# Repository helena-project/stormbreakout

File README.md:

stormbreakout
=============

The Helena storm breakout

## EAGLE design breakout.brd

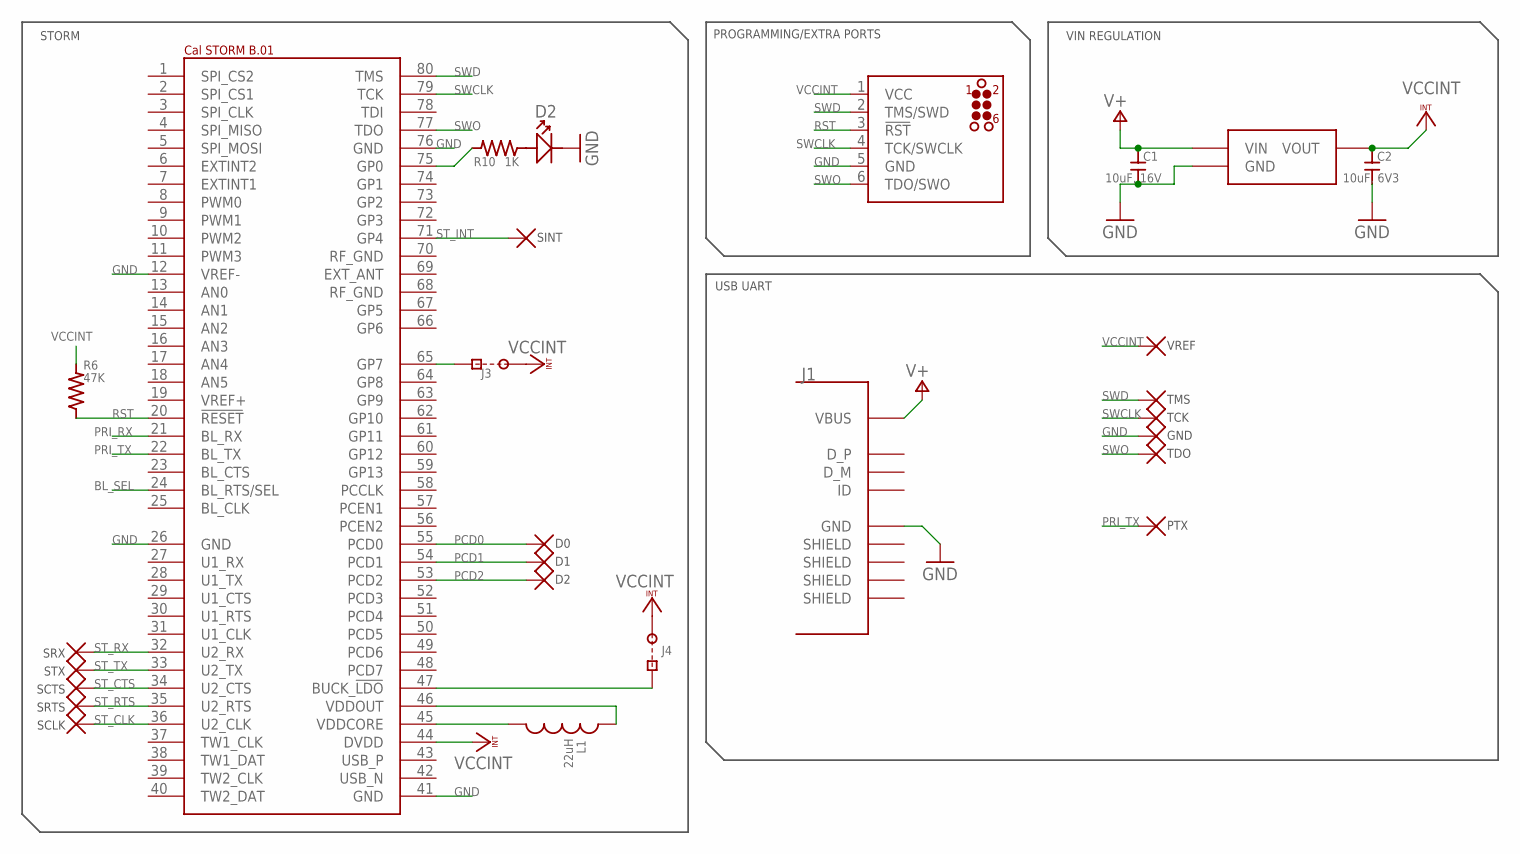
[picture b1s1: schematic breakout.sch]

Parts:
C1: 10uF, 16V; 0805
C2: 10uF, 6V3; C0603
D2: STATLED; LINE_0805
J1: USBSMT; USB_SMT
J3, J4: CUTJ; CUT
J8: JLINK_CONNECT; TC2030-MCP-NL
L1: 22uH; SRN4018
R6: 47K; C0402
R10: 1K; C0402
TP1: VREF; TPP
TP4: TMS; TPP
TP5: TCK; TPP
TP6: GND; TPP
TP7: TDO; TPP
TP10: D2; TPP
TP11: D1; TPP
TP12: D0; TPP
TP13: SRX; TPP
TP14: STX; TPP
TP15: SCTS; TPP
TP16: SRTS; TPP
TP17: SCLK; TPP
TP18: SINT; TPP
TX: PTX; TPP
U1: STORM_B.01; STORM_LANDING
U3: LD1117S33CTR_3V3_REG; SOT223

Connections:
BL_SEL: U1.24 (BL_RTS/SEL)
GND: C1.1, C2.1, D2.LINE (-), J1.5GND (GND), J8.5 (GND), TP6.P$1, U1.12 (VREF-), U1.26 (GND), U1.41 (GND), U1.76 (GND), U3.1 (GND)
unnamed: L1.P$2, U1.45 (VDDCORE)
unnamed: J3.SQ, U1.65 (GP7)
unnamed: L1.P$1, U1.46 (VDDOUT)
unnamed: R10.1, U1.75 (GP0)
unnamed: J4.SQ, U1.47 (BUCK_!LDO!)
unnamed: D2.NOLINE (+), R10.2
PCD0: TP12.P$1, U1.55 (PCD0)
PCD1: TP11.P$1, U1.54 (PCD1)
PCD2: TP10.P$1, U1.53 (PCD2)
PRI_RX: U1.21 (BL_RX)
PRI_TX: TX.P$1, U1.22 (BL_TX)
RST: J8.3 (!RST!), R6.2, U1.20 (!RESET!)
ST_CLK: TP17.P$1, U1.36 (U2_CLK)
ST_CTS: TP15.P$1, U1.34 (U2_CTS)
ST_INT: TP18.P$1, U1.71 (GP4)
ST_RTS: TP16.P$1, U1.35 (U2_RTS)
ST_RX: TP13.P$1, U1.32 (U2_RX)
ST_TX: TP14.P$1, U1.33 (U2_TX)
SWCLK: J8.4 (TCK/SWCLK), TP5.P$1, U1.79 (TCK)
SWD: J8.2 (TMS/SWD), TP4.P$1, U1.80 (TMS)
SWO: J8.6 (TDO/SWO), TP7.P$1, U1.77 (TDO)
V+: C1.2, J1.1VBUS (VBUS), U3.3 (VIN)
VCCINT: C2.2, J3.R, J4.R, J8.1 (VCC), R6.1, TP1.P$1, U1.44 (DVDD), U3.2 (VOUT)

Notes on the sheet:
STORM
USB UART
PROGRAMMING/EXTRA PORTS
VIN REGULATION

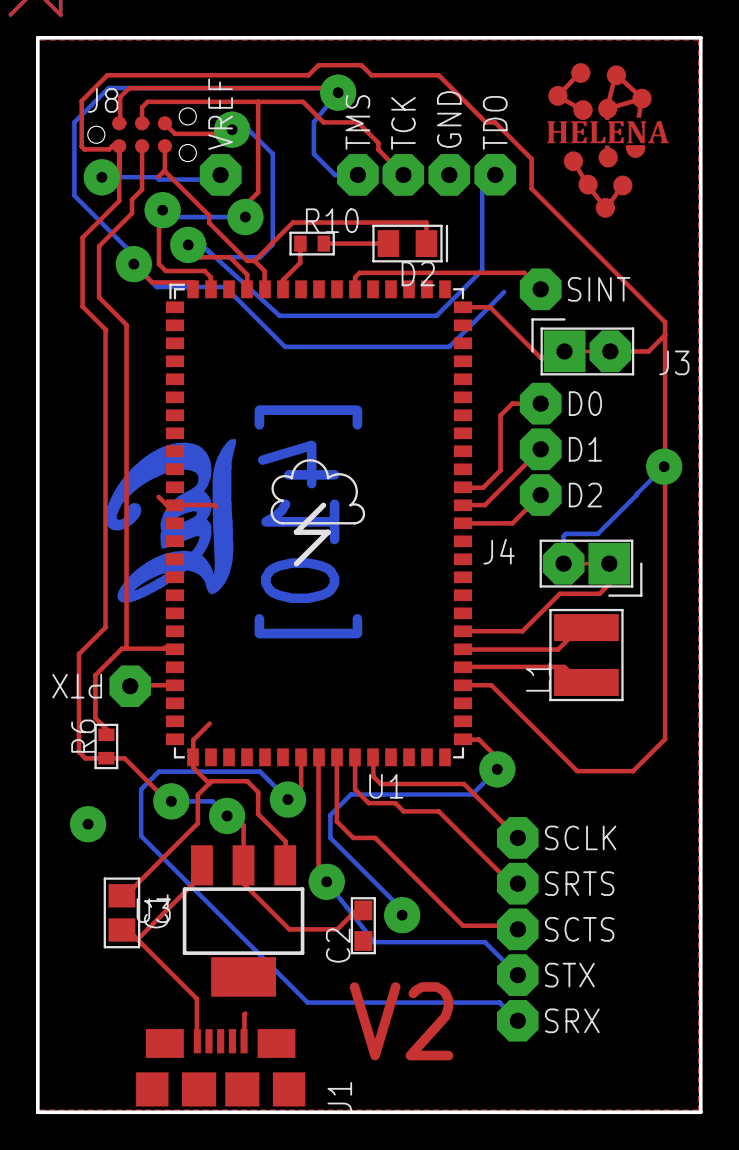
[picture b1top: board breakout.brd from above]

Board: 2 copper layers, 36.8 x 59.7 mm, 27 parts (0 on the bottom side), 23 nets.

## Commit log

2014-10-02 Add breakout board

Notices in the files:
parts and their libraries:
storm: ©2009 ROFA.cz
